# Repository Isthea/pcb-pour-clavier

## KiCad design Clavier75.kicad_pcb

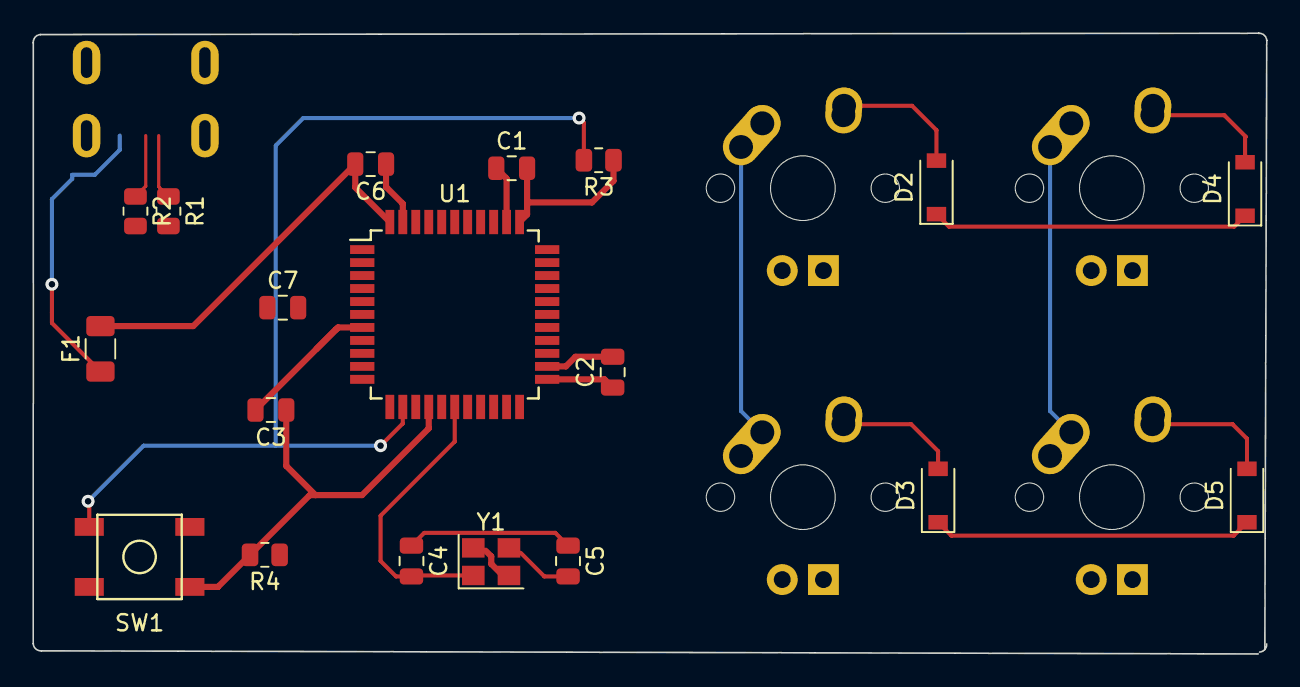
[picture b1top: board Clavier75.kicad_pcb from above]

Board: 2 copper layers, 76.0 x 38.3 mm, 24 parts (1 on the bottom side), 21 nets.

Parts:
C1, C2, C3: 0.1uF; C_0805_2012Metric
C4, C5: 22pF; C_0805_2012Metric
C6: 10uF; C_0805_2012Metric
C7: 1uF; C_0805_2012Metric
D2, D3, D4, D5: SOD-123; D_SOD-123
F1: 500mA; Fuse_1206_3216Metric
MX1, MX3, MX4, MX5: MX-NoLED; MX-1U
R1, R2: 22; R_0805_2012Metric
R3, R4: 10k; R_0805_2012Metric
SW1: SW_Push; SKQG-1155865
U1: ATmega32U4-A; TQFP-44_10x10mm_P0.8mm
USB1: Molex-0548190589
Y1: 16MHz; Crystal_SMD_3225-4Pin_3.2x2.5mm

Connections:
+5V: C1.2, C2.2, C3.2, C6.2, F1.2, R3.1, U1.2 (UVCC), U1.7 (VBUS), U1.14 (VCC), U1.24 (AVCC), U1.34 (VCC), U1.44 (AVCC)
/COL0: MX1.1 (COL), MX3.1 (COL), U1.29 (PB5)
/COL1: MX4.1 (COL), MX5.1 (COL), U1.28 (PB4)
/D+: R2.1, USB1.3 (D+)
/D-: R1.1, USB1.4 (D-)
/ROW0: D2.1 (K), D4.1 (K), U1.27 (PD7)
/ROW1: D3.1 (K), D5.1 (K), U1.30 (PB6)
GND: C1.1, C2.1, C3.1, C6.1, C7.1, R4.2, SW1.1, U1.5 (UGND), U1.15 (GND), U1.23 (GND), U1.35 (GND), U1.43 (GND), USB1.1 (GND), Y1.2, Y1.4
unnamed: C4.1, C5.1
unnamed: C4.2, U1.17 (XTAL1), Y1.1
unnamed: C5.2, U1.16 (XTAL2), Y1.3
unnamed: C7.2, U1.6 (UCAP)
unnamed: D2.2 (A), MX1.2 (ROW)
unnamed: D3.2 (A), MX3.2 (ROW)
unnamed: D4.2 (A), MX4.2 (ROW)
unnamed: D5.2 (A), MX5.2 (ROW)
unnamed: R1.2, U1.3 (D-)
unnamed: R2.2, U1.4 (D+)
unnamed: R3.2, SW1.2, U1.13 (~RESET)
unnamed: R4.1, U1.33 (~HWB/PE2)
VCC: F1.1, USB1.5 (VBUS)

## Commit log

2022-12-26 debut
2022-12-26 dossiers pour les trucs de kicad
2022-12-26 Create sym-lib-table
2022-12-26 Create fp-lib-table
2022-12-26 caramel
2022-12-27 hehehehehehe
2022-12-27 googoogaga
2022-12-27 rsdfsdfsdffsdfdsfss
